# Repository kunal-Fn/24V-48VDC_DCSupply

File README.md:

# 24V-48VDC_DCSupply

flyback transfromer based DC-DC boost conveter based on 3843 PWM IC

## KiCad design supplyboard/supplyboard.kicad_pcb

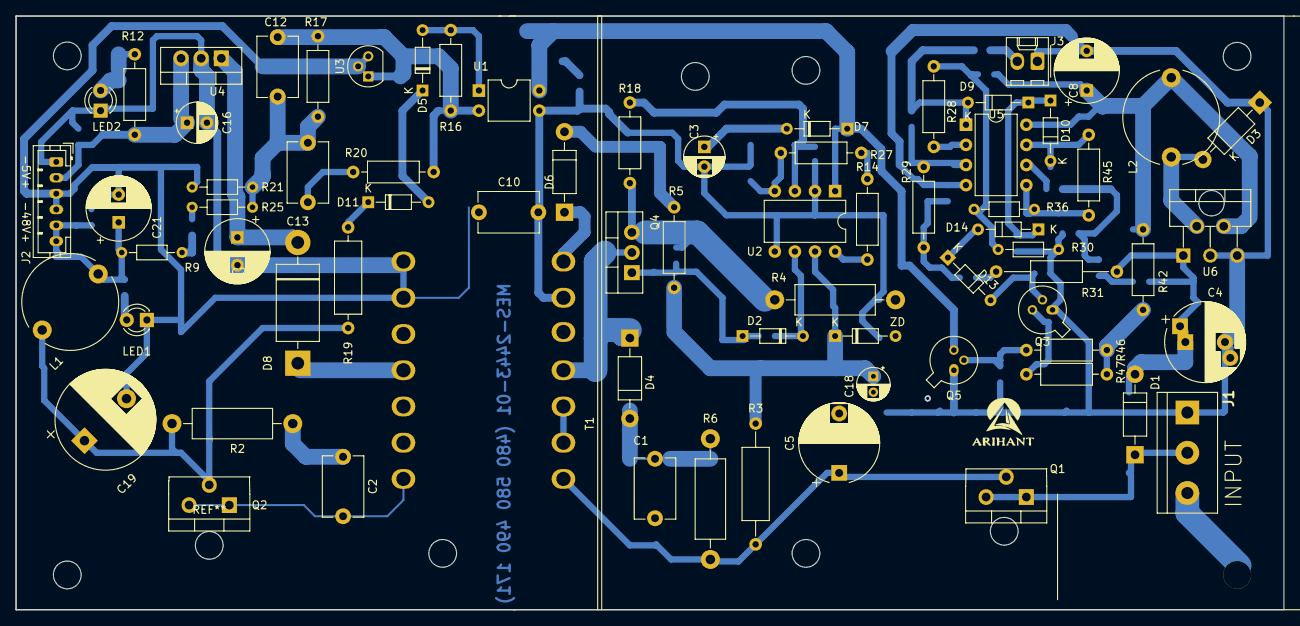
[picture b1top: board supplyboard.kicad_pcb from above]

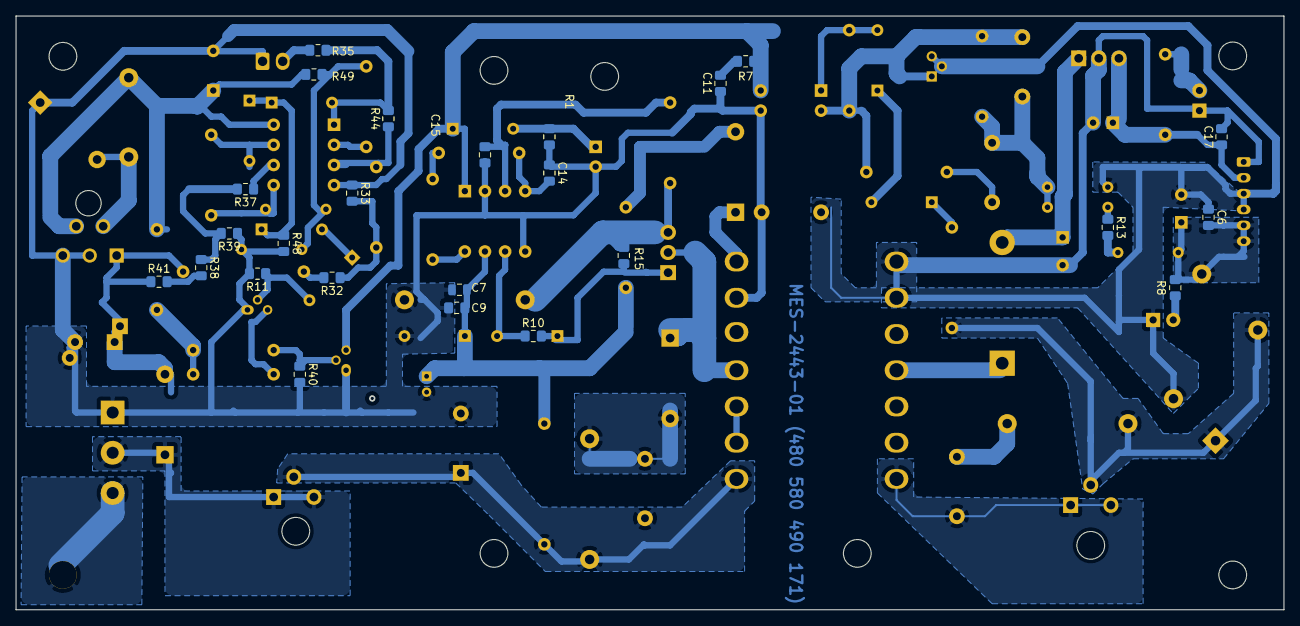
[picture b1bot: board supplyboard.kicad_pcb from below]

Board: 2 copper layers, 160.0 x 74.9 mm, 97 parts (25 on the bottom side), 56 nets.

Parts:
C1, C2, C10, C12, C13: C; C_Disc_D7.5mm_W5.0mm_P7.50mm
C3, C16: CP; CP_Radial_D5.0mm_P2.50mm
C4: CP; CP_Radial_D10.0mm_P5.00mm_P7.50mm
C5: CP; CP_Radial_D10.0mm_P7.50mm
C6, C11, C14, C15, C17: C; C_0805_2012Metric_Pad1.15x1.40mm_HandSolder
C7: C; C_0805_2012Metric
C8: CP; CP_Radial_D8.0mm_P5.00mm
C9: CP; C_0805_2012Metric_Pad1.15x1.40mm_HandSolder
C18: CP; CP_Radial_D4.0mm_P2.00mm
C19: CP; CP_Radial_D12.5mm_P7.50mm
C20: CP; CP_Radial_D8.0mm_P3.50mm
C21: C; CP_Radial_D8.0mm_P3.50mm
D1, D3: 1N4007; D_DO-41_SOD81_P10.16mm_Horizontal
D2, D7, D9, D10, D13, D14: 4148; D_DO-34_SOD68_P7.62mm_Horizontal
D4: D; D_DO-41_SOD81_P10.16mm_Horizontal
D5, D11: 24V; D_DO-34_SOD68_P7.62mm_Horizontal
D6: 4148; D_DO-41_SOD81_P10.16mm_Horizontal
D8: DIODE; D_DO-201AD_P15.24mm_Horizontal
J1: TerminalBlock_bornier-3_P5.08mm
J2: FEMALE 06; JST_PH_B6B-PH-K_1x06_P2.00mm_Vertical
J3: Conn_01x02; Molex_KK-254_AE-6410-02A_1x02_P2.54mm_Vertical
L1, L2: L; L_Radial_D12.0mm_P10.00mm_Neosid_SD12_style1
LED1, LED2: GREEN; LED_D3.0mm
Q1, Q2: MBR20100CT; TO-220-3_Vertical
Q3, Q5: PN2222A; TO-18-3
Q4: IRF540N; TO-220-3_Vertical
R1, R7: 100E; R_0805_2012Metric_Pad1.15x1.40mm_HandSolder
R2: 10E; R_Axial_DIN0411_L9.9mm_D3.6mm_P15.24mm_Horizontal
R3: 4K7 1/2W; R_Axial_DIN0309_L9.0mm_D3.2mm_P15.24mm_Horizontal
R4: E15; R_Axial_DIN0411_L9.9mm_D3.6mm_P15.24mm_Horizontal
R5: 2E2; R_Axial_DIN0207_L6.3mm_D2.5mm_P10.16mm_Horizontal
R6: 47K; R_Axial_DIN0411_L9.9mm_D3.6mm_P15.24mm_Horizontal
R8: 12K; R_0805_2012Metric_Pad1.15x1.40mm_HandSolder
R9: 18K; R_Axial_DIN0204_L3.6mm_D1.6mm_P7.62mm_Horizontal
R10: R; R_0805_2012Metric_Pad1.15x1.40mm_HandSolder
R11, R13, R15, R37, R40: 10K; R_0805_2012Metric_Pad1.15x1.40mm_HandSolder
R12: 1k2; R_Axial_DIN0207_L6.3mm_D2.5mm_P10.16mm_Horizontal
R14, R28, R29, R46: 10K; R_Axial_DIN0207_L6.3mm_D2.5mm_P10.16mm_Horizontal
R16: 2K2; R_Axial_DIN0207_L6.3mm_D2.5mm_P10.16mm_Horizontal
R17: 1M; R_Axial_DIN0207_L6.3mm_D2.5mm_P10.16mm_Horizontal
R18, R47: 1K; R_Axial_DIN0207_L6.3mm_D2.5mm_P10.16mm_Horizontal
R19: 470E; R_Axial_DIN0309_L9.0mm_D3.2mm_P12.70mm_Horizontal
R20, R27: 100E; R_Axial_DIN0207_L6.3mm_D2.5mm_P10.16mm_Horizontal
R21: R; R_Axial_DIN0204_L3.6mm_D1.6mm_P7.62mm_Horizontal
R25: 1K; R_Axial_DIN0204_L3.6mm_D1.6mm_P7.62mm_Horizontal
R30: 100E; R_Axial_DIN0204_L3.6mm_D1.6mm_P7.62mm_Horizontal
R31: 1K5; R_Axial_DIN0207_L6.3mm_D2.5mm_P15.24mm_Horizontal
R32, R38: 27K; R_0805_2012Metric_Pad1.15x1.40mm_HandSolder
R33, R35, R39: 15K; R_0805_2012Metric_Pad1.15x1.40mm_HandSolder
R36: 10K; R_Axial_DIN0204_L3.6mm_D1.6mm_P7.62mm_Horizontal
R41: 47K; R_0805_2012Metric_Pad1.15x1.40mm_HandSolder
R42: 12K; R_Axial_DIN0207_L6.3mm_D2.5mm_P10.16mm_Horizontal
R44: 394K; R_0805_2012Metric_Pad1.15x1.40mm_HandSolder
R45: 270K; R_Axial_DIN0207_L6.3mm_D2.5mm_P10.16mm_Horizontal
R48, R49: 4K7; R_0805_2012Metric_Pad1.15x1.40mm_HandSolder
T1: SM_FB; Transformer_EPCOS_B66359J1014T_Vertical
U1: EL817; DIP-4_W7.62mm
U2: UC3843_DIP8; DIP-8_W7.62mm
U3: TL431D; TO-92
U4: L7805; TO-220-3_Vertical
U5: LM358N_NOPB; DIP-8_W7.62mm
U6: LM2575-12BU; TO-220-5_P3.4x3.7mm_StaggerOdd_Lead3.8mm_Vertical
ZD: 4148; D_DO-34_SOD68_P7.62mm_Horizontal

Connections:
5V: C16.1, C17.1, J2.2, R12.1, U4.3
48V: C6.2, C21.2, J2.5, J2.6, L1.2, R8.2, R9.2
358IN: D1.1, J1.2, Q1.1, Q1.3
/INPUTB: R36.2, R45.1, U5.5
/Qin: D9.1, D10.1, D14.1, R48.1
Earth: C3.2, C4.2, C5.2, C6.1, C7.2, C8.2, C9.2, C10.1, C10.2, C11.1, C14.1, C15.1, C16.2, C17.2, C18.2, C19.2, C20.2, C21.1, D3.1, J1.1, J2.1, J2.3, J2.4, J3.1, LED1.1, LED2.1, Q3.1, Q5.1, R1.1, R4.1, R11.2, R21.1, R30.2, R33.1, R39.1, R40.2, R48.2, T1.2, T1.7, U1.3, U2.2, U2.5, U3.2, U3.3, U4.2, U5.4, U6.3, U6.5, ZD.2
unnamed: C1.1, D4.2, R6.2
unnamed: C1.2, C5.1, Q1.2, R3.1, R6.1, T1.4
unnamed: C2.1, R2.2
unnamed: C2.2, Q2.1, Q2.3, T1.14
unnamed: C3.1, D7.2, R1.2
unnamed: C4.1, D1.2, R31.1, R41.1, U6.1
unnamed: C8.1, L2.2, R35.1, R42.2, U5.8, U6.4
unnamed: C11.2, R7.2
unnamed: C12.1, C13.2, R17.2, R21.2, R25.1
unnamed: C12.2, R16.2, R17.1, R20.2, U1.2, U3.1
unnamed: C13.1, R20.1
unnamed: C14.2, R27.1, U2.4
unnamed: C15.2, R18.1, U2.3
unnamed: D6.2, R5.1
unnamed: C20.1, D8.2, U4.1
unnamed: D2.1, Q4.1, R10.2, R15.1
unnamed: D2.2, R10.1, U2.6
unnamed: D3.2, L2.1, U6.2
unnamed: D4.1, Q4.2, T1.3
unnamed: D5.2, R16.1, U1.1
unnamed: D6.1, T1.1
unnamed: D8.1, T1.6
unnamed: D9.2, R44.2, R49.1, U5.1
unnamed: D10.2, R45.2, U5.7
unnamed: D11.1, R19.2
unnamed: D5.1, D11.2
unnamed: D13.1, D14.2
unnamed: D13.2, Q3.2, R11.1
unnamed: J3.2, R49.2
unnamed: LED1.2, R8.1
unnamed: LED2.2, R12.2
unnamed: Q3.3, R47.1
unnamed: Q4.3, R4.2, R15.2, R18.2
unnamed: Q5.2, R40.1, R46.2
unnamed: R13.1, R25.2
unnamed: R9.1, R13.2
unnamed: R14.1, U2.8
unnamed: R14.2, R27.2
unnamed: R28.1, R30.1, R35.2, R36.1
unnamed: R28.2, U5.2
unnamed: R29.1, R44.1, U5.3
unnamed: R29.2, R32.1, R33.2
unnamed: R31.2, R32.2
unnamed: R37.1, U5.6
unnamed: R37.2, R38.1, R39.2
unnamed: R38.2, R41.2
unnamed: R42.1, R46.1, R47.2
OPTO_2: C19.1, L1.1, Q2.2, R2.1, R19.1
OPTO_POS+: D7.1, Q5.3, R7.1, U1.4, U2.1
TO_FB1: C7.1, C9.1, C18.1, R3.2, R5.2, U2.7, ZD.1

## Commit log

2021-01-10 finalgerber
